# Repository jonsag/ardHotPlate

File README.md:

# ardHotPlate
An arduino used to control a reflow hotplate

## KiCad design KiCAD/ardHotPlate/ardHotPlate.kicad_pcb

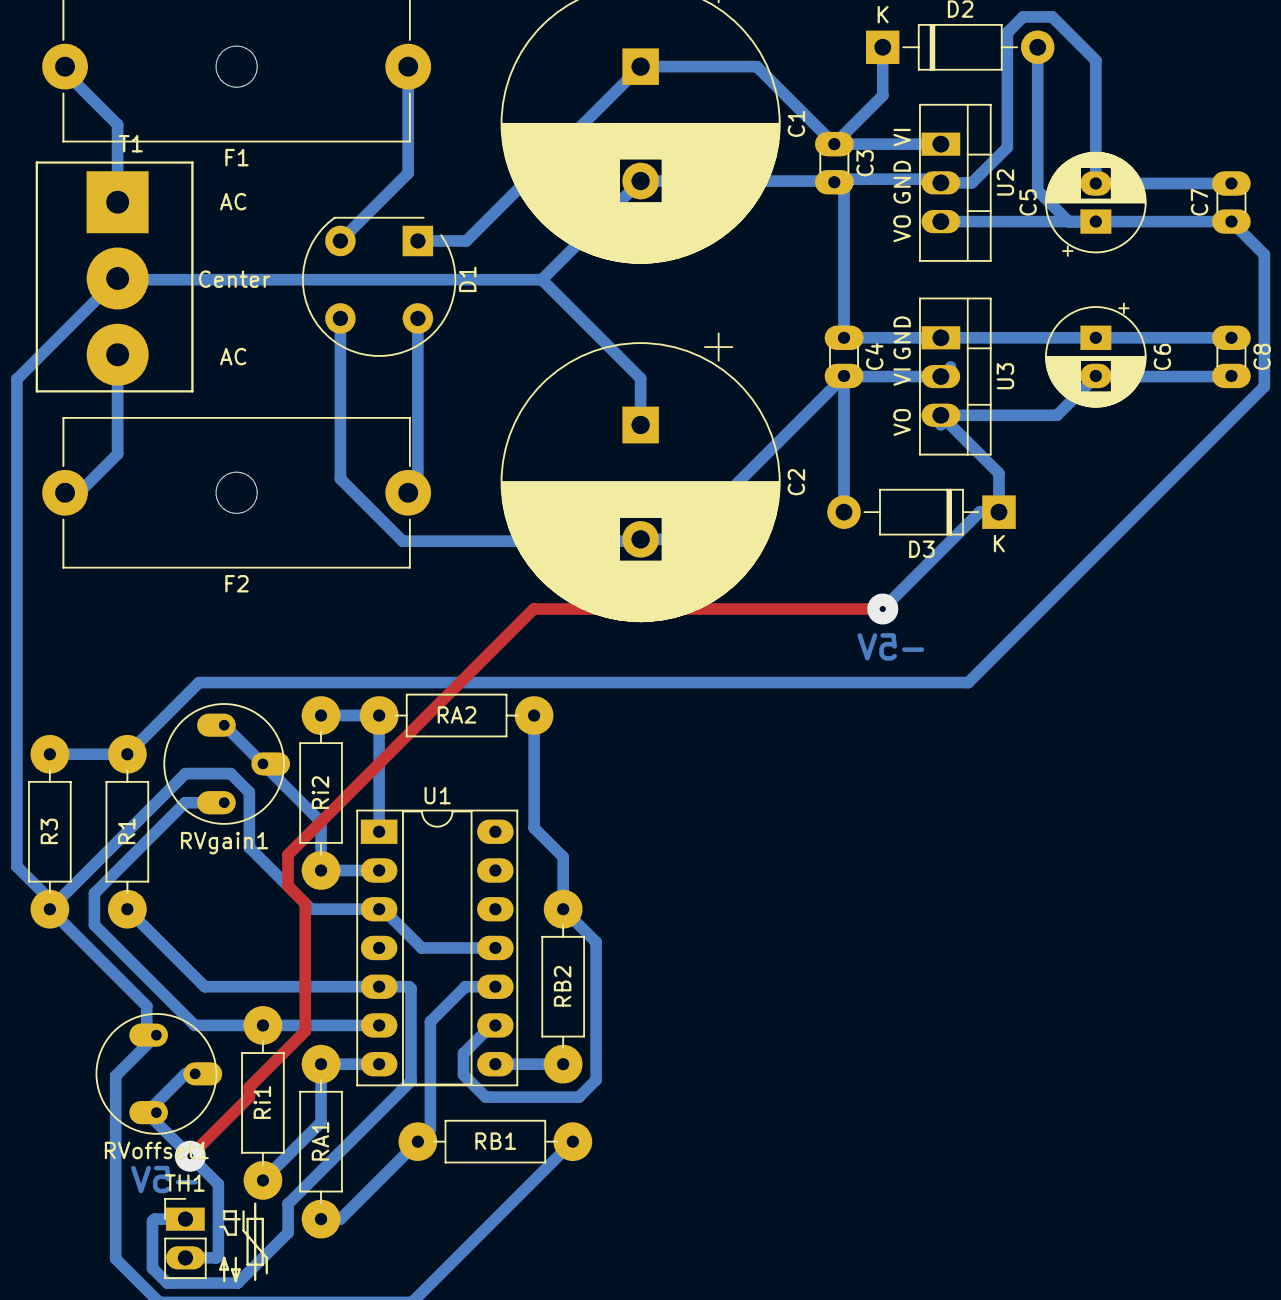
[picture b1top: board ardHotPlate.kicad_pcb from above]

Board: 2 copper layers, 28 parts (0 on the bottom side), 17 nets.

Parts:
C1, C2: 4700u; CP_Radial_D18.0mm_P7.50mm
C3, C4, C7, C8: 0.1u; C_Disc_D3.0mm_W1.6mm_P2.50mm_larg
C5, C6: 220u; CP_Radial_D6.3mm_P2.50mm_large
D1: D_Bridge_+A-A; Diode_Bridge_Round_D9.8mm
D2, D3: 1N4001; D_DO-41_SOD81_P10.16mm_Horizontal
F1, F2: Fuse; Fuseholder_Cylinder-5x20mm_Schurter_0031_8201_Horizontal_Op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
R1, R3: 3.3k; R_Axial_DIN0207_L6.3mm_D2.5mm_P10.16mm_Horizontal_larger_pa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
RA1, RA2: 8.2k; R_Axial_DIN0207_L6.3mm_D2.5mm_P10.16mm_Horizontal_larger_pa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
RB1, RB2: 47k; R_Axial_DIN0207_L6.3mm_D2.5mm_P10.16mm_Horizontal_larger_pa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
RVgain1: 10k; Potentiometer_Bourns_3339P_Vertical_large
RVoffset1: 500; Potentiometer_Bourns_3339P_Vertical_large
Ri1, Ri2: 3.9k; R_Axial_DIN0207_L6.3mm_D2.5mm_P10.16mm_Horizontal_larger_pa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
T1: Transformer_dual_secondary_center_common; 3-pole_screw_terminal_2_x_XV_input
TH1: PT100; 2-pin_Thermistor_NTC_large
U1: LM348; DIP-14_W7.62mm_Socket_LongPads
U2: L7805; LM7805_TO-220-3_Vertical_larger
U3: L7905; LM7905_TO-220-3_Vertical_larger

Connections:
+5V: C5.1, C7.1, D2.2, R1.1, R3.1, U2.3
-5V: C6.2, C8.2, D3.1, RVoffset1.2, RVoffset1.3, TH1.2, U3.3
GND: C1.2, C2.1, C3.2, C4.1, C5.2, C6.1, C7.2, C8.1, R3.2, RB1.1, RVoffset1.1, T1.2, U1.3, U1.11, U2.2, U3.1
unnamed: C1.1, C3.1, D1.1, D2.1, U2.1
unnamed: C2.2, C4.2, D1.3, D3.2, U3.2
unnamed: D1.2, F1.1
unnamed: D1.4, F2.1
unnamed: F1.2, T1.1
unnamed: F2.2, T1.3
unnamed: R1.2, TH1.1, U1.5
unnamed: RA1.1, RB1.2, U1.10
unnamed: RA1.2, Ri1.2, U1.7
unnamed: RA2.1, RB2.2, U1.9
unnamed: RA2.2, Ri2.1, U1.1
unnamed: RVgain1.1, RVgain1.2, Ri2.2, U1.2
unnamed: RVgain1.3, Ri1.1, U1.6
TempRaw: RB2.1, U1.8

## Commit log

2021-10-02 test sketch
2021-10-02 spice and cad
2021-10-02 faulty diode footprint
2022-06-26 schematics
2022-06-26 kicad6
2022-06-26 new pio
2022-06-26 new code with PID and PWM output
2022-06-26 minor
2022-06-27 LCD interface
